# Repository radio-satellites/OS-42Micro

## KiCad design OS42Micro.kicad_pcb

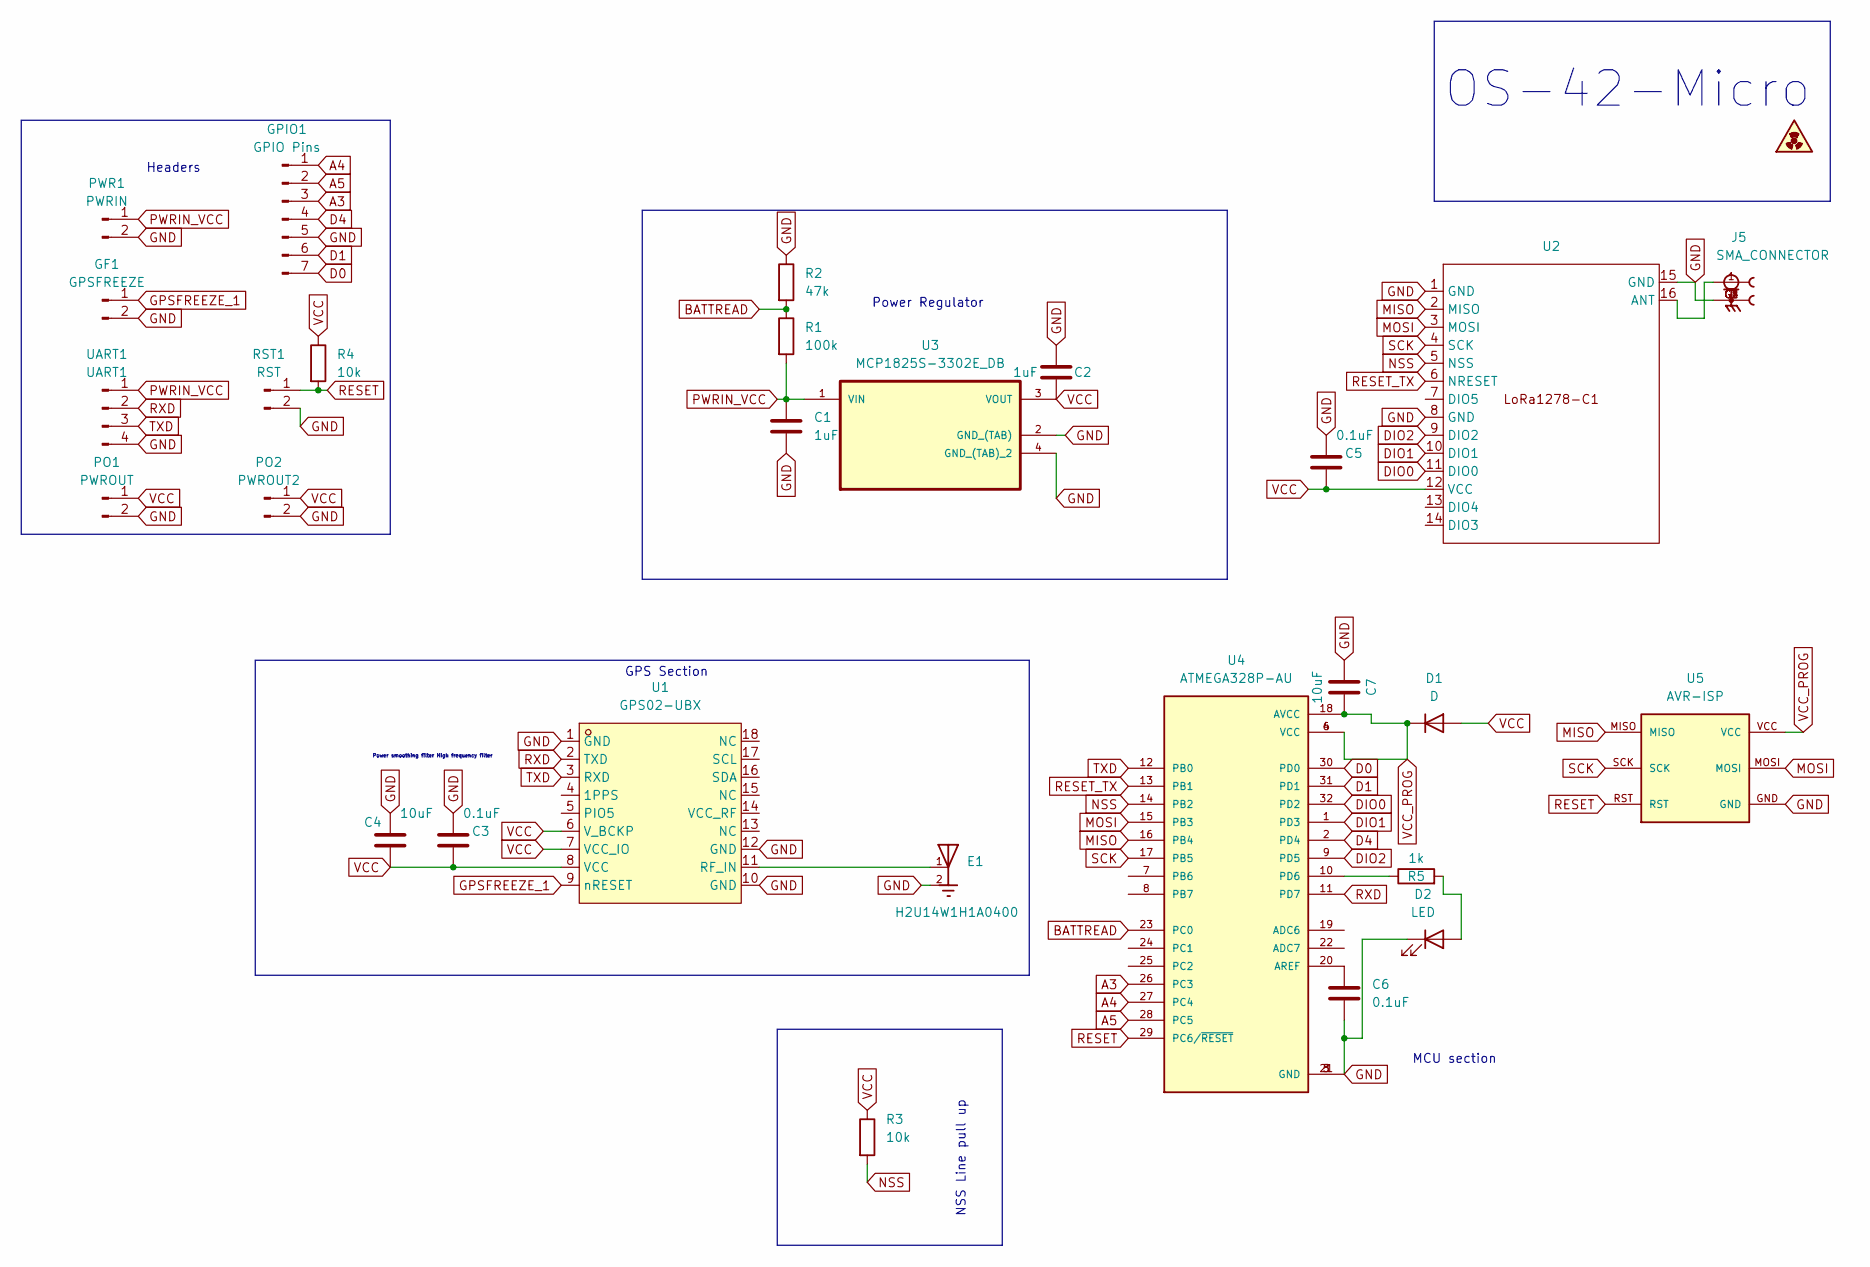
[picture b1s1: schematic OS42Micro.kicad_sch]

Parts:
C1, C2: 1uF; C_0805_2012Metric_Pad1.18x1.45mm_HandSolder
C3, C5, C6: 0.1uF; C_0805_2012Metric_Pad1.18x1.45mm_HandSolder
C4, C7: 10uF; C_0805_2012Metric_Pad1.18x1.45mm_HandSolder
D1: D; D_1206_3216Metric_Pad1.42x1.75mm_HandSolder
D2: LED; LED_1206_3216Metric_Pad1.42x1.75mm_HandSolder
E1: H2U14W1H1A0400; XCVR_H2U14W1H1A0400; PARTREV I
GF1: GPSFREEZE; PinSocket_1x02_P2.54mm_Vertical
GPIO1: GPIO Pins; PinSocket_1x07_P2.54mm_Vertical
J5: SMA_CONNECTOR; LPRS_SMA_CONNECTOR; PARTREV 1.3
PO1: PWROUT; PinSocket_1x02_P2.54mm_Vertical
PO2: PWROUT2; PinSocket_1x02_P2.54mm_Vertical
PWR1: PWRIN; PinSocket_1x02_P2.54mm_Vertical
R1: 100k; R_2010_5025Metric_Pad1.40x2.65mm_HandSolder
R2: 47k; R_2010_5025Metric_Pad1.40x2.65mm_HandSolder
R3: 10k; LED_1206_3216Metric_Pad1.42x1.75mm_HandSolder
R4: 10k; R_1206_3216Metric_Pad1.30x1.75mm_HandSolder
R5: 1k; R_1206_3216Metric_Pad1.30x1.75mm_HandSolder
RST1: RST; PinSocket_1x02_P2.54mm_Vertical
U1: GPS02-UBX; GPS02; LCSC Part C5356636
U2: LoRa1278
U3: MCP1825S-3302E_DB; SOT230P700X180-4N
U4: ATMEGA328P-AU; QFP80P900X900X120-32N; PARTREV 8271A
U5: AVR-ISP
UART1: UART1; PinSocket_1x04_P2.54mm_Vertical

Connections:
A3: GPIO1.3, U4.26 (PC3)
A4: GPIO1.1, U4.27 (PC4)
A5: GPIO1.2, U4.28 (PC5)
BATTREAD: R1.1, R2.2, U4.23 (PC0)
D0: GPIO1.7, U4.30 (PD0)
D1: GPIO1.6, U4.31 (PD1)
D4: GPIO1.4, U4.2 (PD4)
DIO0: U2.11 (DIO0), U4.32 (PD2)
DIO1: U2.10 (DIO1), U4.1 (PD3)
DIO2: U2.9 (DIO2), U4.9 (PD5)
GND: C1.2, C2.2, C3.1, C4.1, C5.1, C6.2, C7.2, D2.1 (K), E1.2, GF1.2, GPIO1.5, J5.G1, J5.G2, J5.G3, J5.G4, PO1.2, PO2.2, PWR1.2, R2.1, RST1.2, U1.1 (GND), U1.10 (GND), U1.12 (GND), U2.1 (GND), U2.8 (GND), U2.15 (GND), U3.2 (GND_(TAB)), U3.4 (GND_(TAB)_2), U4.3 (GND), U4.5 (GND), U4.21 (GND), U5.GND, UART1.4
GPSFREEZE_1: GF1.1, U1.9 (nRESET)
MISO: U2.2 (MISO), U4.16 (PB4), U5.MISO
MOSI: U2.3 (MOSI), U4.15 (PB3), U5.MOSI
NSS: R3.2, U2.5 (NSS), U4.14 (PB2)
unnamed: D2.2 (A), R5.2
unnamed: E1.1, U1.11 (RF_IN)
unnamed: J5.1, U2.16 (ANT)
unnamed: C6.1, U4.20 (AREF)
unnamed: R5.1, U4.10 (PD6)
PWRIN_VCC: C1.1, PWR1.1, R1.2, U3.1 (VIN), UART1.1
RESET: R4.2, RST1.1, U4.29 (PC6/~RESET), U5.RST
RESET_TX: U2.6 (NRESET), U4.13 (PB1)
RXD: U1.2 (TXD), U4.11 (PD7), UART1.2
SCK: U2.4 (SCK), U4.17 (PB5), U5.SCK
TXD: U1.3 (RXD), U4.12 (PB0), UART1.3
VCC: C2.1, C3.2, C4.2, C5.2, D1.2 (A), PO1.1, PO2.1, R3.1, R4.1, U1.6 (V_BCKP), U1.7 (VCC_IO), U1.8 (VCC), U2.12 (VCC), U3.3 (VOUT)
VCC_PROG: C7.1, D1.1 (K), U4.4 (VCC), U4.6 (VCC), U4.18 (AVCC), U5.VCC

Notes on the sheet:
MCU section
Headers
NSS Line pull up
Power Regulator
Power smoothing filter High frequency filter
OS-42-Micro
GPS Section

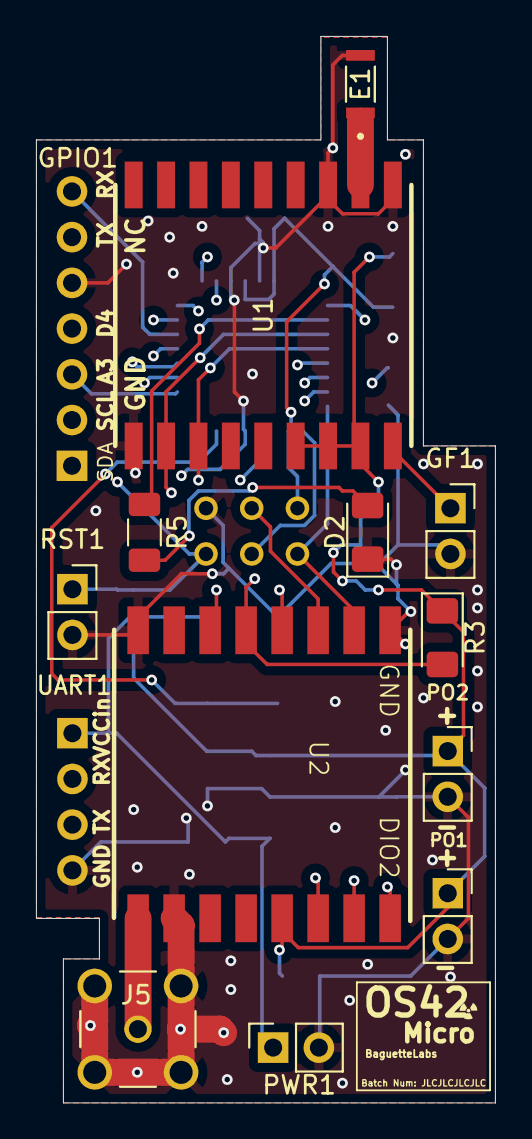
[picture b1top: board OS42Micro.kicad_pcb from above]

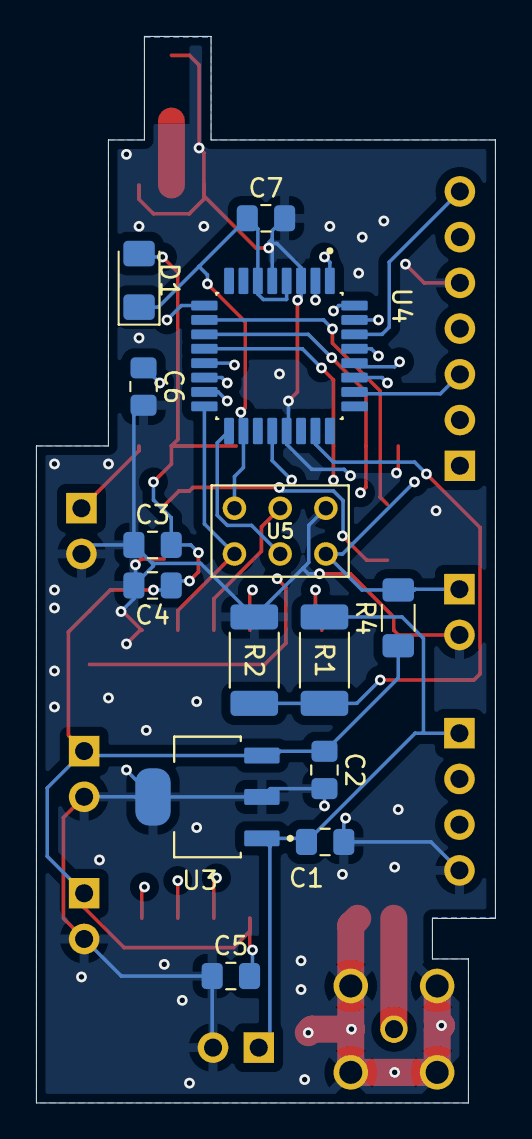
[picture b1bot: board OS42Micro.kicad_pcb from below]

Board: 4 copper layers, 25.5 x 59.2 mm, 28 parts (14 on the bottom side), 28 nets.

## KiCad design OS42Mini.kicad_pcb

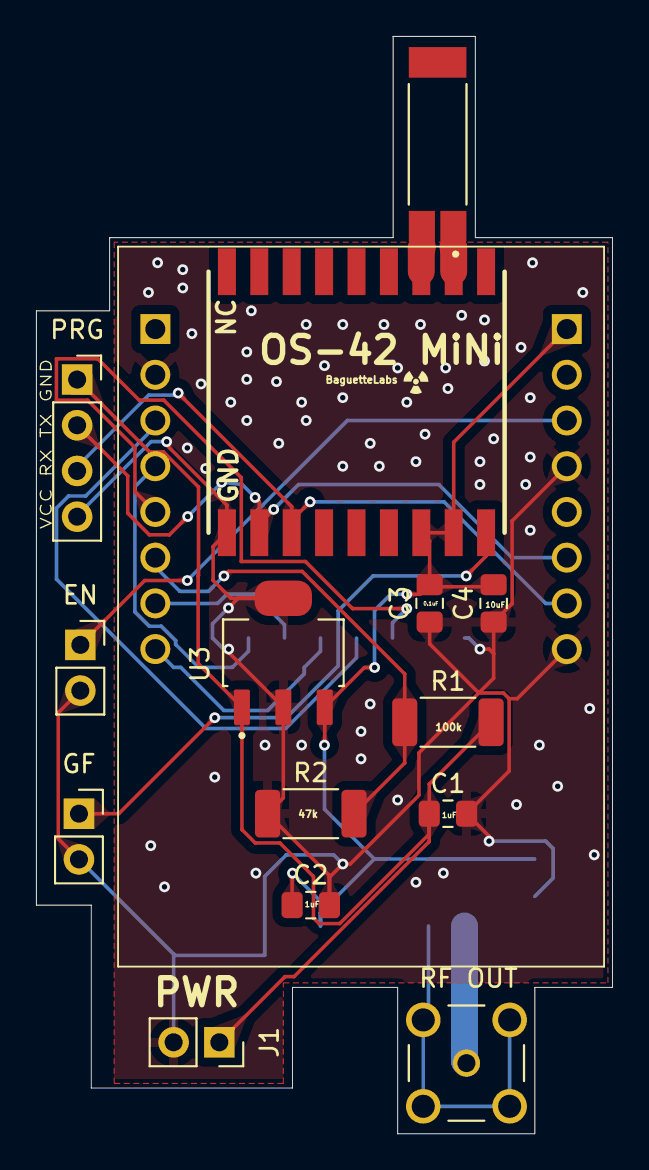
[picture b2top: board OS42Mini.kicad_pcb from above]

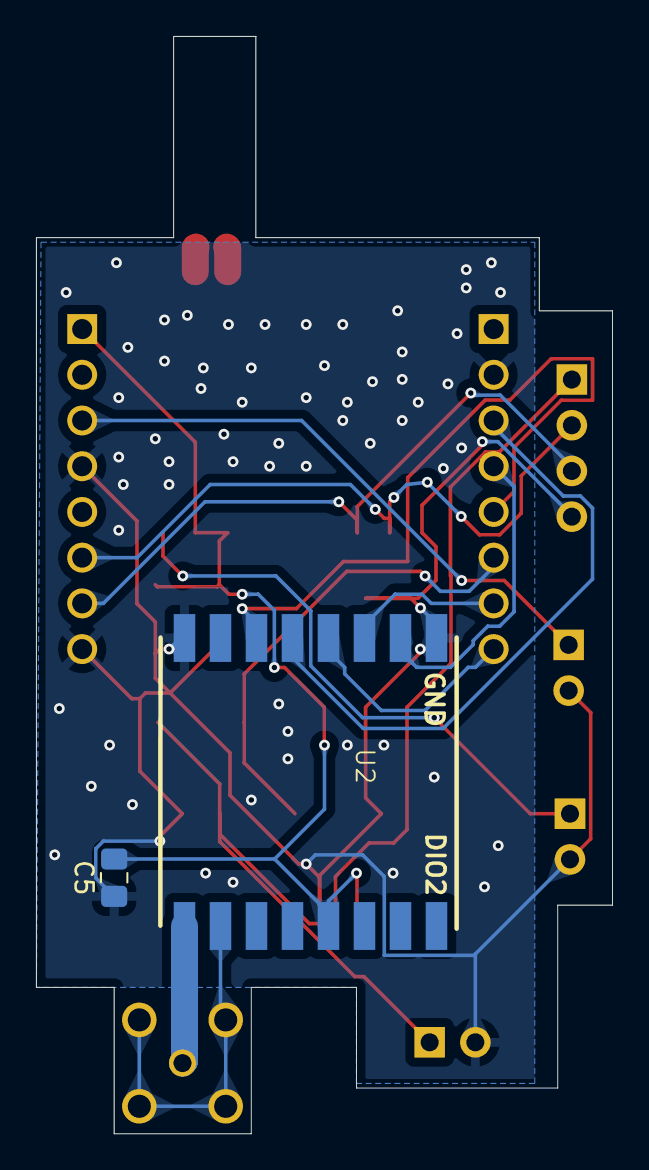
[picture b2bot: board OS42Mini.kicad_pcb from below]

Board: 2 copper layers, 32.0 x 61.0 mm, 17 parts (2 on the bottom side), 17 nets.

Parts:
C1, C2: C; C_0805_2012Metric_Pad1.18x1.45mm_HandSolder
C3, C5: 0.1uF; C_0805_2012Metric_Pad1.18x1.45mm_HandSolder
C4: 10uF; C_0805_2012Metric_Pad1.18x1.45mm_HandSolder
E1: W3010; XCVR_W3010
EN: PROG_EN; PinSocket_1x02_P2.54mm_Vertical
GF: GPSFREEZE; PinSocket_1x02_P2.54mm_Vertical
IC1: ESP32-CAM; ESP32CAM
J1: PWRIN; PinSocket_1x02_P2.54mm_Vertical
PRG: PROG; PinSocket_1x04_P2.54mm_Vertical
R1: 100k; R_2010_5025Metric_Pad1.40x2.65mm_HandSolder
R2: 47k; R_2010_5025Metric_Pad1.40x2.65mm_HandSolder
RF OUT: SMA_CONNECTOR; LPRS_SMA_CONNECTOR
U1: GPS02-UBX; GPS02
U2: LoRa1278
U3: MCP1825S-3302E_DB; SOT230P700X180-4N

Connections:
ANTGND: E1.2, U1.10 (GND), U1.12 (GND)
BATTREAD: IC1.3 (IO14), R1.1, R2.2
GND: C1.2, C2.2, C3.1, C4.1, C5.1, EN.2, GF.2, IC1.7 (GND_1), IC1.12 (GND_2), IC1.16 (GND_3), J1.2, PRG.4, R2.1, U1.1 (GND), U2.1 (GND), U2.8 (GND), U3.2 (GND_(TAB)), U3.4 (GND_(TAB)_2)
GPSFREEZE_1: GF.1, U1.9 (nRESET)
MISO: IC1.5 (IO13), U2.2 (MISO)
MOSI: IC1.2 (IO2), U2.3 (MOSI)
NSS: IC1.6 (IO12), U2.5 (NSS)
unnamed: RF OUT.G1, RF OUT.G2, RF OUT.G3, RF OUT.G4, U2.15 (GND)
unnamed: E1.1, U1.11 (RF_IN)
unnamed: RF OUT.1, U2.16 (ANT)
PROG_EN: EN.1, IC1.11 (IO0)
PWRIN_VCC: C1.1, J1.1, PRG.1, R1.2, U3.1 (VIN)
RESET: IC1.4 (IO15), U2.6 (NRESET)
RXD: IC1.14 (U0R), PRG.2, U1.2 (TXD)
SCK: IC1.1 (IO4), U2.4 (SCK)
TXD: IC1.15 (U0T), PRG.3, U1.3 (RXD)
VCC: C2.1, C3.2, C4.2, C5.2, IC1.9 (3V3), U1.6 (V_BCKP), U1.7 (VCC_IO), U1.8 (VCC), U2.12 (VCC), U3.3 (VOUT)
